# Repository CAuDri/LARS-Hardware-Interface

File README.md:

# LARS Hardware Interface

This repository contains the schematic, PCB design files and a basic firmware stack for the Hardware Interface of the [Lightweight Autonomous Racing System (LARS)](https://github.com/CAuDri/LARS). 

The board is based on a STM32F4 microcontroller and is designed to interface with various sensors and actuators on the vehicle. The communication with the host PC is done via USB, using [micro-ROS](https://micro.ros.org/) and the underlying [micro-XRCE DDS](https://micro-xrce-dds.docs.eprosima.com/en/latest/).

## License

This project is licensed under the [GNU General Public License v3.0](https://www.gnu.org/licenses/gpl-3.0.en.html). You can freely use, modify, and distribute this code as long as you comply with the terms of the license.

The hardware design files are released under the [CERN Open Hardware Licence v2](https://ohwr.org/cernohl/).

# Hardware

##  Features

### General
- STM32F429 microcontroller (Cortex-M4, 180MHz, 2MB Flash, 256KB RAM)
- Board dimensions: 86 x 86 mm
- SWD interface for programming and debugging
- Boot-/Reset header for flashing via USB
- User- and Reset buttons
- RGB Debug LEDs

### Power
- 5V power supply via XT30 connector or USB (XT30 will be prioritized)
- Power input range: **4.8V - 5.3V**
- "Reverse polarity protection"
- On-board 3.3V voltage regulator
- Switchable 5V output for external devices
- Additional 3.3V and 5V output

### Interfaces
- 2x USB-C (2.0 Fullspeed) for host PC and debugging/flashing
- CAN-Bus (with optional termination)
- 8x I2C
- 3x UART
- 2x SPI
- 2x Servo (with analog feedback)
- 2x WS2812 LED strip 
- Buffered and filtered analog inputs
- Additional Timer channels and GPIOs
- 3.3V and 5V output for external devices

### Protection
- 4A/8A polyfuse on the main power input
- "Rudimentary" reverse polarity protection
- Back-power protection for both power inputs (USB and XT30)
- TVS diodes against voltage spikes on all power rails
- Current limited 5V output (max 2.4 A)
- All data lines are 5V tolerant
- Additional short-circuit, overcurrent and -voltage protection up to ~20V on all interfaces

## PCB-Files

The board was designed in KiCad 9.0. The project file can be found in the `/PCB/KiCad` directory.

Link to the [Schematic](https://github.com/CAuDri/LARS-Hardware-Interface/blob/main/PCB/schematic.pdf).

All PCB design files, a bill of materials and Gerber Files for manufacturing at [JLCPCB](https://jlcpcb.com/) can be found in the `/PCB/manufacturing` directory. They have been exported using the [Fabrication Toolkit](https://github.com/bennymeg/Fabrication-Toolkit) KiCad plugin.

A 3D STEP model of the board can be found in the `/PCB/export` directory.

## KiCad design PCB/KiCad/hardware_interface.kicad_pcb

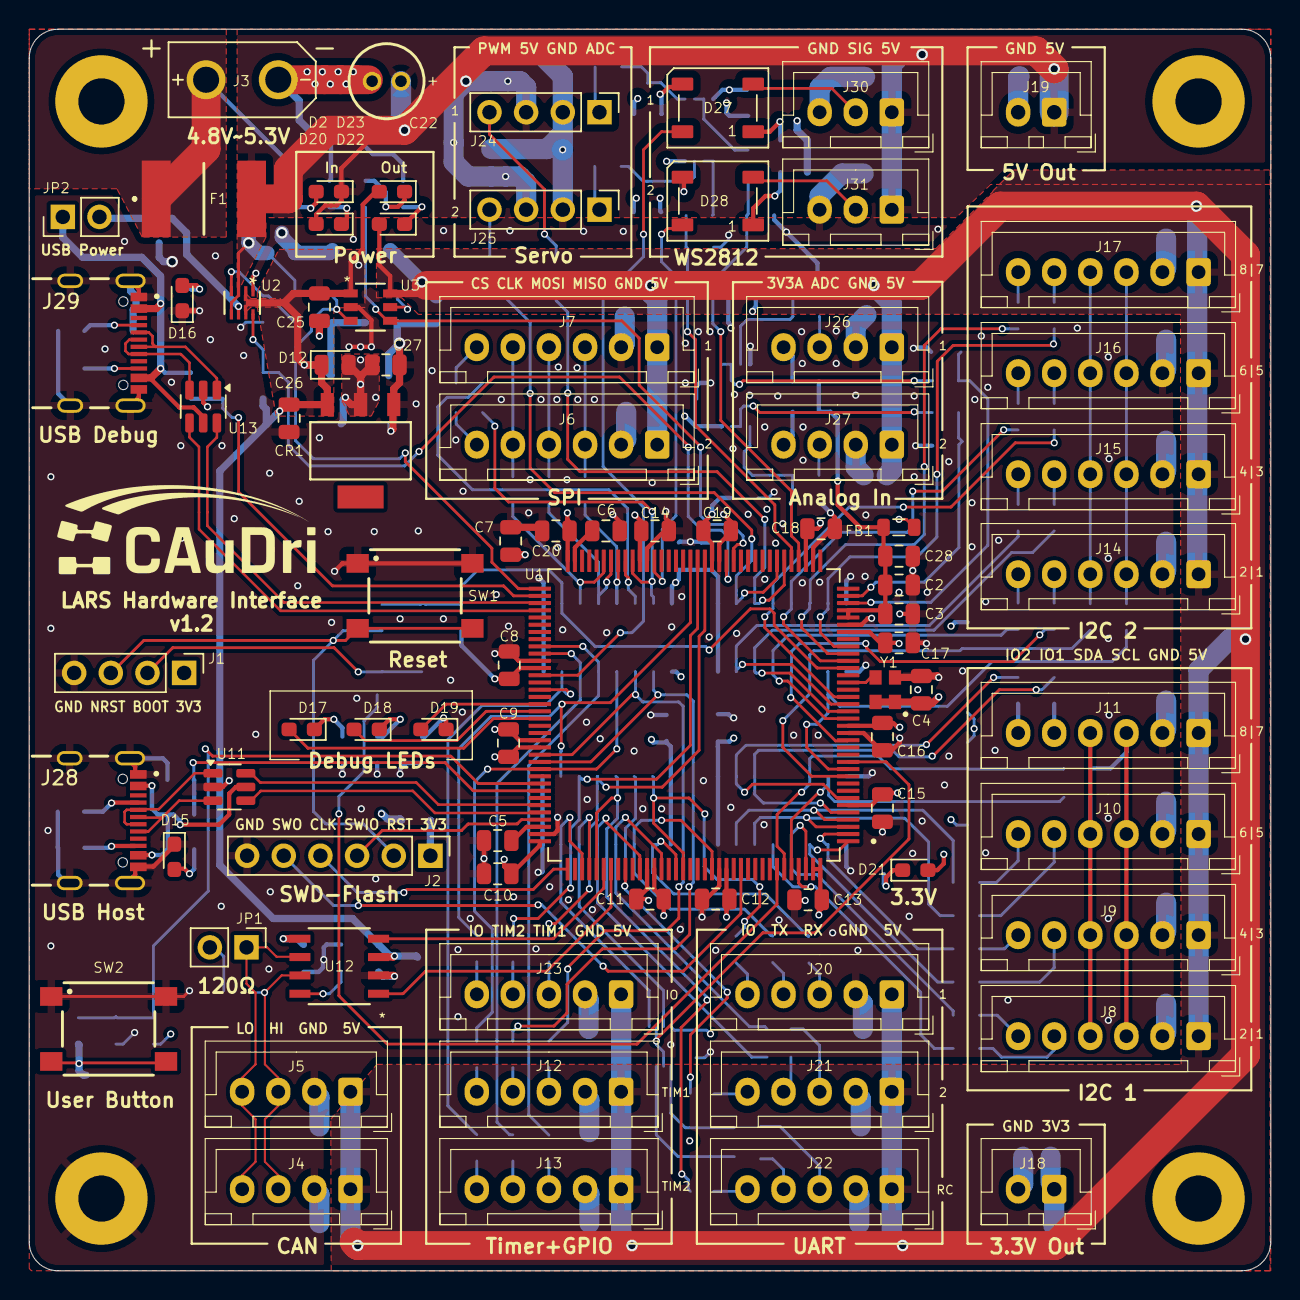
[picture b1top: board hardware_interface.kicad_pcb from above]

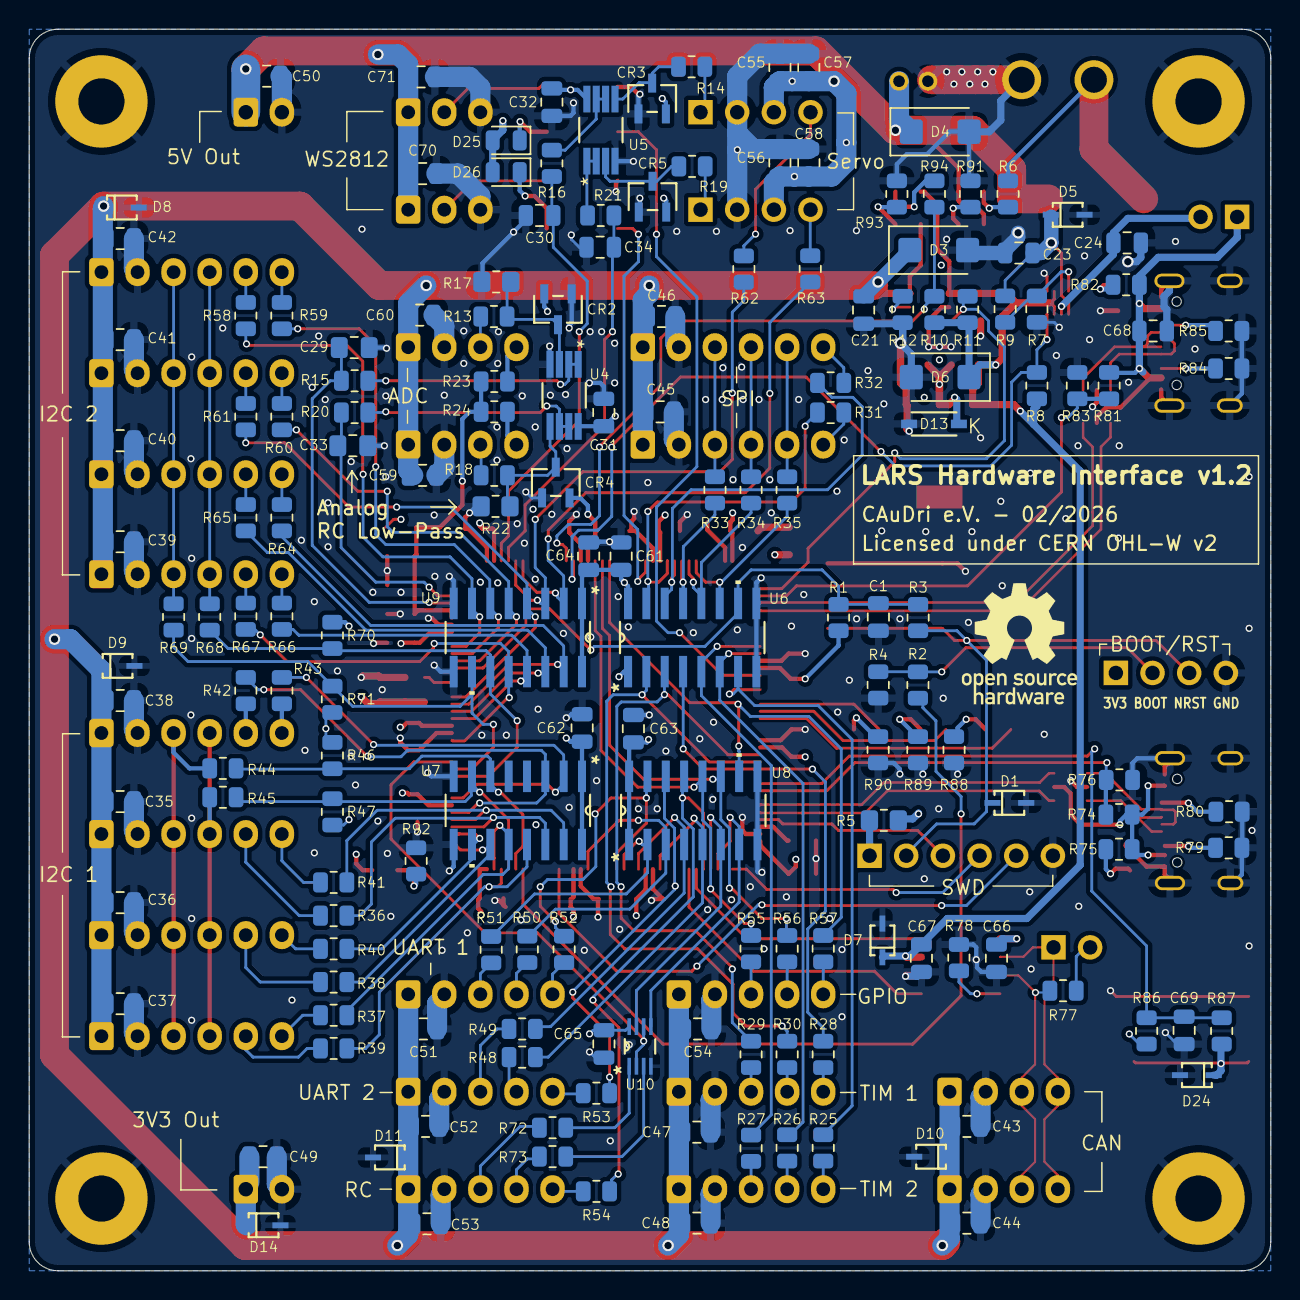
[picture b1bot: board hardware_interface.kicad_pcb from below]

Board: 6 copper layers, 86.0 x 86.0 mm, 255 parts (168 on the bottom side), 178 nets.

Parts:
C1, C3, C4, C8, C9, C10, C11, C12, C13, C14, C15, C16, C17, C18, C19, C20, C30, C31, C32, C34, C35, C36, C37, C38, C39, C40, C41, C42, C43, C44, C45, C46, C47, C48, C49, C50, C51, C52, C53, C54, C57, C58, C59, C60, C61, C62, C63, C64, C65, C66, C67, C70, C71: 100n; C_0805_2012Metric
C2, C5, C6, C24, C26, C68, C69: 2u2; C_0805_2012Metric
C7, C21, C23, C25, C27, C55, C56: 10u; C_0805_2012Metric
C22: 100u; 860020372006
C28: 10n; C_0805_2012Metric
C29, C33: NA; C_0805_2012Metric_Pad1.18x1.45mm_HandSolder
CR1: LD1117AS33TR
CR2, CR3, CR4, CR5: BAT54SFILM
D1, D5, D7, D8, D9, D10, D11, D14, D24: TVS; STS321050U182
D2, D17, D23: Red; LED_0603_1608Metric_Red
D3, D4, D6: 5V6; Z1SMA5.6
D12, D25, D26: 0.7V; D_0805_2012Metric
D13: 3V3; BZT52C3V3
D15, D16, D18, D20, D21, D22: Green; LED_0603_1608Metric_Green
D19: Blue; LED_0603_1608Metric_Blue
D27, D28: WS2812B; LED_WS2812B_PLCC4_5.0x5.0mm_P3.2mm
F1: 2920L400; 2920L400_15MR
FB1: FBMH2012HM221-T8; L_0805_2012Metric
G1: CAuDri-Logo; CAuDri Logo
G2: LOGO; OSHWA Logo
H1, H2, H3, H4: MountingHole; MountingHole_3.2mm_M3_Pad
J1: Reset Header; PinHeader_1x04_P2.54mm_Vertical
J2: SWD Flash; PinHeader_1x06_P2.54mm_Vertical
J3: XT30; XT30UPB-M
J4, J5: CAN1; JST_XH_B4B-XH-A_1x04_P2.50mm_Vertical
J6, J7: SPI1; JST_XH_B6B-XH-A_1x06_P2.50mm_Vertical
J8, J9, J10, J11: I2C1; JST_XH_B6B-XH-A_1x06_P2.50mm_Vertical
J12: TIM1; JST_XH_B5B-XH-A_1x05_P2.50mm_Vertical
J13: TIM2; JST_XH_B5B-XH-A_1x05_P2.50mm_Vertical
J14, J15, J16, J17: I2C2; JST_XH_B6B-XH-A_1x06_P2.50mm_Vertical
J18: 3.3V Out; JST_XH_B2B-XH-A_1x02_P2.50mm_Vertical
J19: 5V Out; JST_XH_B2B-XH-A_1x02_P2.50mm_Vertical
J20: UART1; JST_XH_B5B-XH-A_1x05_P2.50mm_Vertical
J21: UART2; JST_XH_B5B-XH-A_1x05_P2.50mm_Vertical
J22: RC; JST_XH_B5B-XH-A_1x05_P2.50mm_Vertical
J23: GPIO; JST_XH_B5B-XH-A_1x05_P2.50mm_Vertical
J24: Servo 1; PinHeader_1x04_P2.54mm_Vertical
J25: Servo 2; PinHeader_1x04_P2.54mm_Vertical
J26: Analog 1; JST_XH_B4B-XH-A_1x04_P2.50mm_Vertical
J27: Analog 2; JST_XH_B4B-XH-A_1x04_P2.50mm_Vertical
J28: USB1; GCT_USB4105-GF-A
J29: USB2; GCT_USB4105-GF-A
J30: LED1; JST_XH_B3B-XH-A_1x03_P2.50mm_Vertical
J31: LED2; JST_XH_B3B-XH-A_1x03_P2.50mm_Vertical
JP1: CAN1; PinHeader_1x02_P2.54mm_Jumper
JP2: USB Power; PinHeader_1x02_P2.54mm_Jumper
R1, R4, R7, R86: 10k; R_0805_2012Metric
R2, R6, R9, R13, R14, R16, R18, R19, R21, R74, R78, R81, R87, R88, R89, R90, R91, R92, R93, R94: 1k; R_0805_2012Metric
R3, R15, R20, R25, R26, R27, R28, R29, R30, R31, R32, R33, R34, R35, R36, R37, R38, R39, R40, R41, R42, R43, R48, R49, R50, R51, R52, R53, R54, R55, R56, R57, R58, R59, R60, R61, R62, R63, R64, R65, R66, R67, R72, R73, R75, R82: 220; R_0805_2012Metric
R5: 0R; R_0805_2012Metric_Pad1.20x1.40mm_HandSolder
R8, R10, R11, R79, R80, R84, R85: 5k1; R_0805_2012Metric
R12, R23, R24, R44, R45, R68, R69, R77: 120; R_0805_2012Metric
R17, R22: NA; R_0805_2012Metric_Pad1.20x1.40mm_HandSolder
R46, R47, R70, R71, R76, R83: 2k2; R_0805_2012Metric
SW1: Reset; 430182043816
SW2: User Button; 430182043816
U1: STM32F429ZIT6TR
U2: TPS2117DRLR; PTPS2117DRLR
U3: MIC2039AYM6-TR
U4, U5: OPA2834IDGKR
U6, U7, U8, U9: SN74S1051DR
U10: SN74LVC2G86DCUR; SN74LVC2G86
U11, U13: USBLC6-2SC6; SOT-23-6
U12: TCAN1057AVDRQ1
Y1: IQXO-791 8.00MHz; WE-SPXO_IQXO-791

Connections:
5V_USB: C24.1, JP2.2 (B), U2.6 (VIN2)
+3V3: C4.1, C7.1, C8.1, C9.1, C10.1, C11.1, C12.1, C13.1, C14.1, C15.1, C16.1, C17.1, C18.1, C19.1, C20.1, C27.1, C31.1, C32.1, C49.1, C61.1, C62.1, C63.1, C64.1, C65.1, C66.1, CR1.2 (VOUT), CR2.2, CR3.2, CR4.2, CR5.2, D12.2 (A), D13.1 (K), D14.1 (K), D21.2 (A), FB1.1, J1.1, J18.1, R1.2, R5.2, R46.2, R47.2, R70.2, R71.2, R86.1, U1.6 (VBAT), U1.17 (VDD), U1.30 (VDD), U1.39 (VDD), U1.52 (VDD), U1.62 (VDD), U1.72 (VDD), U1.84 (VDD), U1.95 (VDD), U1.108 (VDD), U1.121 (VDD), U1.131 (VDD), U1.143 (PDR_ON), U1.144 (VDD), U4.8 (VS+), U5.8 (VS+), U6.1 (VCC), U6.16 (VCC), U7.1 (VCC), U7.16 (VCC), U8.1 (VCC), U8.16 (VCC), U9.1 (VCC), U9.16 (VCC), U10.8 (VCC), U12.5 (VIO), Y1.1 (E/D), Y1.4 (+VS)
+3V3A: C2.1, C3.1, C28.1, FB1.2, R23.2, R24.2, U1.32 (VREF+), U1.33 (VDDA)
+5V: C25.1, C26.1, C67.1, CR1.3 (VIN), D6.1 (K), D7.1 (K), D12.1 (K), D23.2 (A), D25.2 (A), D26.2 (A), R8.1, R10.2, R11.2, U2.2 (VOUT), U2.7 (VOUT), U3.1 (VIN), U12.3 (VCC)
+5V_OUT: C21.1, C35.1, C36.1, C37.1, C38.1, C39.1, C40.1, C41.1, C42.1, C43.1, C44.1, C45.1, C46.1, C47.1, C48.1, C51.1, C52.1, C53.1, C54.1, C59.1, C60.1, D3.1 (K), D8.1 (K), D9.1 (K), D10.1 (K), D11.1 (K), D22.2 (A), J4.1, J5.1, J6.1, J7.1, J8.1, J9.1, J10.1, J11.1, J12.1, J13.1, J14.1, J15.1, J16.1, J17.1, J20.1, J21.1, J22.1, J23.1, J26.1, J27.1, U3.6 (VOUT)
+5V_PS: C22.1, C23.1, C50.1, C55.1, C56.1, C57.1, C58.1, C70.1, C71.1, D2.1 (K), D4.1 (K), D5.1 (K), D20.2 (A), F1.2, J19.1, J24.3, J25.3, J30.1, J31.1, R9.2, U2.3 (VIN1), U2.5 (MODE)
/Analog/ANALOG1_OP_IN: CR2.3, R13.2, R17.1, U4.3 (VIN1+)
/Analog/ANALOG1_OP_OUT: R15.1, U4.1 (VOUT1), U4.2 (VIN1-)
/Analog/ANALOG2_OP_IN: CR4.3, R18.2, R22.1, U4.5 (VIN2+)
/Analog/ANALOG2_OP_OUT: R20.1, U4.6 (VIN2-), U4.7 (VOUT2)
/Analog/SERVO1_OP_IN: CR3.3, R14.2, U5.5 (VIN2+)
/Analog/SERVO1_OP_OUT: R16.1, U5.6 (VIN2-), U5.7 (VOUT2)
/Analog/SERVO2_OP_IN: CR5.3, R19.2, U5.3 (VIN1+)
/Analog/SERVO2_OP_OUT: R21.1, U5.1 (VOUT1), U5.2 (VIN1-)
/LEDs/LED1_OUT: D27.2 (DOUT), J30.2
/LEDs/LED1_VDD: D25.1 (K), D27.1 (VDD)
/LEDs/LED2_OUT: D28.2 (DOUT), J31.2
/LEDs/LED2_VDD: D26.1 (K), D28.1 (VDD)
/LEDs/LED_3V3: D21.1 (K), R92.1
/LEDs/LED_5V_OUT: D22.1 (K), R93.1
/LEDs/LED_5V_PS: D20.1 (K), R91.1
/LEDs/LED_BLUE: D19.1 (K), R90.1
/LEDs/LED_EXT_OC: D23.1 (K), R94.1
/LEDs/LED_GREEN: D18.1 (K), R89.1
/LEDs/LED_RED: D17.1 (K), R88.1
/LEDs/USER_BTN: D24.1 (K), R87.2, SW2.2
/Microcontroller/BOOT0: J1.2, R2.1, R4.2
/Microcontroller/RESET: D1.1 (K), J1.3, J2.2, R3.1, SW1.2
/Microcontroller/STM_BOOT0: R2.2, U1.138 (BOOT0)
/Microcontroller/STM_OSC_IN: U1.23 (PH0), Y1.3 (OUT)
/Microcontroller/STM_VCAP1: C6.1, U1.71 (VCAP_1)
/Microcontroller/STM_VCAP2: C5.1, U1.106 (VCAP_2)
/Power Distribution/MUX_PR1: R7.1, R9.1, U2.4 (PR1)
/Power Distribution/PS_ILIMIT: R12.1, U3.5 (ILIMIT)
/Power Distribution/PWR_IN: F1.1, J3.2 (PWR), R6.2
/USB + CAN Bus/USB1_CC1: J28.A5 (CC1), R80.1
/USB + CAN Bus/USB1_CC2: J28.B5 (CC2), R79.1
/USB + CAN Bus/USB1_D_IN+: J28.A6 (D+), J28.B6 (D+), U11.3 (I/O2)
/USB + CAN Bus/USB1_D_IN-: J28.A7 (D-), J28.B7 (D-), U11.1 (I/O1)
/USB + CAN Bus/USB1_VBUS_IN: J28.A4_B9 (VBUS), J28.B4_A9 (VBUS), R74.2, R75.1, U11.5 (VBUS)
/USB + CAN Bus/USB2_CC1: J29.A5 (CC1), R85.1
/USB + CAN Bus/USB2_CC2: J29.B5 (CC2), R84.1
/USB + CAN Bus/USB2_D_IN+: J29.A6 (D+), J29.B6 (D+), U13.3 (I/O2)
/USB + CAN Bus/USB2_D_IN-: J29.A7 (D-), J29.B7 (D-), U13.1 (I/O1)
/USB + CAN Bus/USB2_VBUS_IN: C68.1, J29.A4_B9 (VBUS), J29.B4_A9 (VBUS), JP2.1 (A), R81.2, R82.1, U13.5 (VBUS)
ANALOG_IN1: J26.3, R13.1
ANALOG_IN1': C29.1, R15.2, U1.34 (PA0)
ANALOG_IN2: J27.3, R18.1
ANALOG_IN2': C33.1, R20.2, U1.35 (PA1)
CAN1_N: J4.4, J5.4, JP1.1 (A), U12.6 (CANL)
CAN1_P: J4.3, J5.3, R77.1, U12.7 (CANH)
CAN1_RX: U1.114 (PD0), U12.4 (RXD)
CAN1_TX: U1.115 (PD1), U12.1 (TXD)
DEBUG_LED_BLUE: D19.2 (A), U1.89 (PG4)
DEBUG_LED_GREEN: D18.2 (A), U1.90 (PG5)
DEBUG_LED_RED: D17.2 (A), U1.91 (PG6)
GND: C1.2, C2.2, C3.2, C4.2, C5.2, C6.2, C7.2, C8.2, C9.2, C10.2, C11.2, C12.2, C13.2, C14.2, C15.2, C16.2, C17.2, C18.2, C19.2, C20.2, C21.2, C22.2, C23.2, C24.2, C25.2, C26.2, C27.2, C28.2, C29.2, C30.2, C31.2, C32.2, C33.2, C34.2, C35.2, C36.2, C37.2, C38.2, C39.2, C40.2, C41.2, C42.2, C43.2, C44.2, C45.2, C46.2, C47.2, C48.2, C49.2, C50.2, C51.2, C52.2, C53.2, C54.2, C55.2, C56.2, C57.2, C58.2, C59.2, C60.2, C61.2, C62.2, C63.2, C64.2, C65.2, C66.2, C67.2, C68.2, C69.2, C70.2, C71.2, CR1.1 (GND), CR2.1, CR3.1, CR4.1, CR5.1, D1.2 (A), D3.2 (A), D4.2 (A), D5.2 (A), D6.2 (A), D7.2 (A), D8.2 (A), D9.2 (A), D10.2 (A), D11.2 (A), D13.2 (A), D14.2 (A), D15.1 (K), D16.1 (K), D24.2 (A), D27.3 (VSS), D28.3 (VSS), H1.1, H2.1, H3.1, H4.1, J1.4, J2.6, J3.1 (GND), J4.2, J5.2, J6.2, J7.2, J8.2, J9.2, J10.2, J11.2, J12.2, J13.2, J14.2, J15.2, J16.2, J17.2, J18.2, J19.2, J20.2, J21.2, J22.2, J23.2, J24.2, J25.2, J26.2, J27.2, J28.A1_B12 (GND), J28.B1_A12 (GND), J28.S1 (SHIELD), J29.A1_B12 (GND), J29.B1_A12 (GND), J29.S1 (SHIELD), J30.3, J31.3, R4.1, R7.2, R12.2, R17.2, R22.2, R76.2, R78.1, R79.2, R80.2, R83.2, R84.2, R85.2, R88.2, R89.2, R90.2, R91.2, R92.2, R93.2, SW1.1, SW2.1, U1.16 (VSS), U1.31 (VSSA), U1.38 (VSS), U1.51 (VSS), U1.61 (VSS), U1.83 (VSS), U1.94 (VSS), U1.107 (VSS), U1.120 (VSS), U1.130 (VSS), U2.1 (GND), U3.2 (GND), U4.4 (VS-), U5.4 (VS-), U6.8 (GND), U6.9 (GND), U7.8 (GND), U7.9 (GND), U8.8 (GND), U8.9 (GND), U9.8 (GND), U9.9 (GND), U10.4 (GND), U11.2 (GND), U12.2 (GND), U13.2 (GND), Y1.2 (GND)
GPIO1: J23.3, R55.2
GPIO1': R55.1, U1.53 (PF13), U8.12 (D09)
GPIO2: J23.4, R56.2
GPIO2': R56.1, U1.54 (PF14), U8.11 (D08)
GPIO3: J23.5, R57.2
GPIO3': R57.1, U1.55 (PF15), U8.10 (D07)
I2C1_IO1: J8.5, R39.2
I2C1_IO1': R39.1, U1.141 (PE0), U7.13 (D10)
I2C1_IO2: J8.6, R38.2
I2C1_IO2': R38.1, U1.142 (PE1), U7.12 (D09)
I2C1_IO3: J9.5, R37.2
I2C1_IO3': R37.1, U1.1 (PE2), U7.11 (D08)
I2C1_IO4: J9.6, R36.2
I2C1_IO4': R36.1, U1.2 (PE3), U7.10 (D07)
I2C1_IO5: J10.5, R40.2
I2C1_IO5': R40.1, U1.3 (PE4), U7.14 (D11)
I2C1_IO6: J10.6, R41.2
I2C1_IO6': R41.1, U1.4 (PE5), U7.15 (D12)
I2C1_IO7: J11.5, R43.2
I2C1_IO7': R43.1, U1.5 (PE6), U7.3 (D02)
I2C1_IO8: J11.6, R42.2
I2C1_IO8': R42.1, U1.7 (PC13), U7.2 (D01)
I2C1_SCL: J8.3, J9.3, J10.3, J11.3, R44.2
I2C1_SCL': R44.1, R46.1, U1.139 (PB8), U7.6 (D05)
I2C1_SDA: J8.4, J9.4, J10.4, J11.4, R45.2
I2C1_SDA': R45.1, R47.1, U1.140 (PB9), U7.7 (D06)
I2C2_IO1: J14.5, R67.2
I2C2_IO1': R67.1, U1.15 (PF5), U9.12 (D09)
I2C2_IO2: J14.6, R66.2
I2C2_IO2': R66.1, U1.18 (PF6), U9.13 (D10)
I2C2_IO3: J15.5, R65.2
I2C2_IO3': R65.1, U1.19 (PF7), U9.14 (D11)
I2C2_IO4: J15.6, R64.2
I2C2_IO4': R64.1, U1.20 (PF8), U9.15 (D12)
I2C2_IO5: J16.5, R61.2
I2C2_IO5': R61.1, U1.21 (PF9), U9.4 (D03)
I2C2_IO6: J16.6, R60.2
I2C2_IO6': R60.1, U1.26 (PC0), U9.5 (D04)
I2C2_IO7: J17.5, R58.2
I2C2_IO7': R59.1, U1.27 (PC1), U9.6 (D05)
I2C2_IO8: J17.6, R59.2
I2C2_IO8': R58.1, U1.28 (PC2), U9.7 (D06)
I2C2_SCL: J14.3, J15.3, J16.3, J17.3, R69.2
I2C2_SCL': R69.1, R71.1, U1.11 (PF1), U9.10 (D07)
I2C2_SDA: J14.4, J15.4, J16.4, J17.4, R68.2
I2C2_SDA': R68.1, R70.1, U1.10 (PF0), U9.11 (D08)
LED1_PWM: D27.4 (DIN), U1.85 (PD14)
LED2_PWM: D28.4 (DIN), U1.60 (PE9)
unnamed: D2.2 (A), R6.1
unnamed: D15.2 (A), R75.2
unnamed: D16.2 (A), R82.2
unnamed: J2.1, R5.1
unnamed: J26.4, R23.1
unnamed: J27.4, R24.1
unnamed: JP1.2 (B), R77.2
unnamed: R72.1, U10.1 (1A)
unnamed: R73.1, U10.3 (2Y)
unnamed: R78.2, U12.8 (S)
PWR_EXT_EN: R11.1, U1.73 (PB12), U3.3 (EN)
PWR_EXT_FAULT: R10.1, R94.2, U1.49 (PF11), U3.4 (*FAULT)
PWR_STATUS: R8.2, U1.50 (PF12), U2.8 (ST)
RC_INVERT: U1.12 (PF2), U10.2 (1B), U10.6 (2B)
RC_IO: J22.5, R54.2
RC_IO': R54.1, U1.113 (PC12), U8.13 (D10)
RC_RX: J22.3, R72.2
RC_RX': U1.112 (PC11), U8.6 (D05), U10.7 (1Y)
RC_TX: J22.4, R73.2
RC_TX': U1.111 (PC10), U8.7 (D06), U10.5 (2A)
SERVO1_ADC: J24.1, R14.1
SERVO1_ADC': C30.1, R16.2, U1.40 (PA4)
SERVO1_PWM: J24.4, R62.2
SERVO1_PWM': R62.1, U1.42 (PA6), U9.3 (D02)
SERVO2_ADC: J25.1, R19.1
SERVO2_ADC': C34.1, R21.2, U1.41 (PA5)
SERVO2_PWM: J25.4, R63.2
SERVO2_PWM': R63.1, U1.43 (PA7), U9.2 (D01)
SPI1_CS1: J6.6, R31.2
SPI1_CS1': R31.1, U1.63 (PE10), U6.15 (D12)
SPI1_CS2: J7.6, R32.2
SPI1_CS2': R32.1, U1.64 (PE11), U6.14 (D11)
SPI1_MISO: J6.4, J7.4, R34.2
SPI1_MISO': R34.1, U1.66 (PE13), U6.12 (D09)
SPI1_MOSI: J6.5, J7.5, R35.2
SPI1_MOSI': R35.1, U1.67 (PE14), U6.11 (D08)
SPI1_SCLK: J6.3, J7.3, R33.2
SPI1_SCLK': R33.1, U1.65 (PE12), U6.13 (D10)
STM_NRST: C1.1, R1.1, R3.2, U1.25 (~NRST), U6.10 (D07)
SWD_SWCLK: J2.4, U1.109 (PA14)
SWD_SWIO: J2.3, U1.105 (PA13)
SWD_SWO: J2.5, U1.133 (PB3)
TIM1_CH1: J12.3, R29.2
TIM1_CH1': R29.1, U1.96 (PC6), U6.3 (D02)
TIM1_CH2: J12.4, R30.2
TIM1_CH2': R30.1, U1.97 (PC7), U6.2 (D01)
TIM1_IO: J12.5, R28.2
TIM1_IO': R28.1, U1.98 (PC8), U6.4 (D03)
TIM2_CH1: J13.3, R27.2
TIM2_CH1': R27.1, U1.81 (PD12), U6.5 (D04)
TIM2_CH2: J13.4, R26.2
TIM2_CH2': R26.1, U1.82 (PD13), U6.6 (D05)
TIM2_IO: J13.5, R25.2
TIM2_IO': R25.1, U1.87 (PG2), U6.7 (D06)
UART1_IO: J20.5, R52.2
UART1_IO': R52.1, U1.125 (PG10), U8.15 (D12)
UART1_RX: J20.3, R51.2
UART1_RX': R51.1, U1.124 (PG9), U8.2 (D01)
UART1_TX: J20.4, R50.2
UART1_TX': R50.1, U1.129 (PG14), U8.3 (D02)
UART2_IO: J21.5, R53.2
UART2_IO': R53.1, U1.117 (PD3), U8.14 (D11)
UART2_RX: J21.3, R49.2
UART2_RX': R49.1, U1.122 (PD6), U8.4 (D03)
UART2_TX: J21.4, R48.2
UART2_TX': R48.1, U1.119 (PD5), U8.5 (D04)
USB1_D+: U1.104 (PA12), U11.4 (I/O2)
USB1_D-: U1.103 (PA11), U11.6 (I/O1)
USB1_VBUS: R74.1, R76.1, U1.101 (PA9)
USB2_D+: U1.76 (PB15), U13.4 (I/O2)
USB2_D-: U1.75 (PB14), U13.6 (I/O1)
USB2_VBUS: R81.1, R83.1, U1.74 (PB13)
USER_BUTTON: C69.1, R86.2, R87.1, U1.100 (PA8)

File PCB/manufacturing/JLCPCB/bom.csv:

Designator,Footprint,Quantity,Value,LCSC Part #
"C1, C10, C11, C12, C13, C14, C15, C16, C17, C18, C19, C20, C3, C30, C31, C32, C34, C35, C36, C37, C38, C39, C4, C40, C41, C42, C43, C44, C45, C46, C47, C48, C49, C50, C51, C52, C53, C56, C57, C58, C59, C60, C61, C62, C63, C64, C65, C66, C69, C70, C8, C9",0805,52,100n,
"C2, C24, C26, C5, C6, C67, C68",0805,7,2u2,
"C21, C23, C25, C27, C54, C55, C7",0805,7,10u,
C22,860020372006,1,100u,
C28,0805,1,10n,
CR1,LD1117AS33TR,1,LD1117AS33TR,
"CR2, CR3, CR4, CR5",BAT54SFILM,4,BAT54SFILM,
"D1, D15, D9",0603,3,Red,
"D10, D12, D13, D14, D7, D8",0603,6,Green,
D11,0603,1,Blue,
"D16, D17, D5",0805,3,0.7V,
"D18, D19",LED_WS2812B_PLCC4_5.0x5.0mm_P3.2mm,2,WS2812B,
"D2, D3, D4",Z1SMA5.6,3,5V6,
D6,BZT52C3V3,1,3V3,
F1,2920L400_15MR,1,2920L400,
FB1,0805,1,FBMH2012HM221-T8,
G1,CAuDri Logo,1,CAuDri-Logo,
J1,PinHeader_1x04_P2.54mm_Vertical,1,Reset Header,
"J10, J11, J8, J9",JST_XH_B6B-XH-A_1x06_P2.50mm_Vertical,4,I2C1,
J12,JST_XH_B5B-XH-A_1x05_P2.50mm_Vertical,1,TIM1,
J13,JST_XH_B5B-XH-A_1x05_P2.50mm_Vertical,1,TIM2,
"J14, J15, J16, J17",JST_XH_B6B-XH-A_1x06_P2.50mm_Vertical,4,I2C2,
J18,JST_XH_B2B-XH-A_1x02_P2.50mm_Vertical,1,3.3V Out,
J19,JST_XH_B2B-XH-A_1x02_P2.50mm_Vertical,1,5V Out,
J2,PinHeader_1x06_P2.54mm_Vertical,1,SWD Flash,
J20,JST_XH_B5B-XH-A_1x05_P2.50mm_Vertical,1,UART1,
J21,JST_XH_B5B-XH-A_1x05_P2.50mm_Vertical,1,UART2,
J22,JST_XH_B5B-XH-A_1x05_P2.50mm_Vertical,1,UART3,
J23,PinHeader_1x04_P2.54mm_Vertical,1,Servo 1,
J24,PinHeader_1x04_P2.54mm_Vertical,1,Servo 2,
J25,JST_XH_B5B-XH-A_1x05_P2.50mm_Vertical,1,GPIO,
J26,JST_XH_B4B-XH-A_1x04_P2.50mm_Vertical,1,Analog 1,
J27,JST_XH_B4B-XH-A_1x04_P2.50mm_Vertical,1,Analog 2,
J28,GCT_USB4105-GF-A,1,USB1,
J29,GCT_USB4105-GF-A,1,USB2,
J3,XT30UPB-M,1,XT30,
J30,JST_XH_B3B-XH-A_1x03_P2.50mm_Vertical,1,LED1,
J31,JST_XH_B3B-XH-A_1x03_P2.50mm_Vertical,1,LED2,
"J4, J5",JST_XH_B4B-XH-A_1x04_P2.50mm_Vertical,2,CAN1,
"J6, J7",JST_XH_B6B-XH-A_1x06_P2.50mm_Vertical,2,SPI1,
JP1,PinHeader_1x02_P2.54mm_Jumper,1,CAN1,
JP2,PinHeader_1x02_P2.54mm_Jumper,1,USB Power,
"R1, R4, R7, R86",0805,4,10k,
"R10, R11, R8",0805,3,4k7,
"R12, R23, R24, R45, R46, R70, R71, R77",0805,8,120,
"R13, R14, R16, R18, R19, R2, R21, R76, R78, R83, R9",0805,11,1k,
"R15, R20, R25, R26, R27, R28, R29, R30, R31, R32, R33, R34, R35, R36, R37, R38, R39, R40, R41, R42, R43, R44, R49, R50, R51, R52, R53, R54, R55, R56, R57, R58, R59, R60, R61, R62, R63, R64, R65, R66, R67, R68, R69, R75, R82, R88, R89, R90, R92",0805,49,220,
"R3, R6, R74, R81, R87, R91, R93, R94",0805,8,470,
"R47, R48, R72, R73",0805,4,2k2,
R5,0805,1,0R,
"R79, R80, R84, R85",0805,4,5k1,
SW1,430182043816,1,Reset,
SW2,430182043816,1,User Button,
U1,STM32F429ZIT6TR,1,STM32F429ZIT6TR,
"U10, U12",SOT-23-6,2,USBLC6-2SC6,
U11,TCAN1057AVDRQ1,1,TCAN1057AVDRQ1,
U2,PTPS2117DRLR,1,TPS2117DRLR,
U3,MIC2039AYM6-TR,1,MIC2039AYM6-TR,
"U4, U5",OPA2834IDGKR,2,OPA2834IDGKR,
"U6, U7, U8, U9",SN74S1051DR,4,SN74S1051DR,
Y1,WE-SPXO_IQXO-791,1,IQXO-791 8.00MHz,

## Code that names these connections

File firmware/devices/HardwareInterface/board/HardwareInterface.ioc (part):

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Mcu.Name=STM32F429ZITx
Mcu.Package=LQFP144
Mcu.UserName=STM32F429ZITx
PA0/WKUP.GPIOParameters=GPIO_Label
PA0/WKUP.GPIO_Label=ANALOG_IN1
PA0/WKUP.Signal=ADCx_IN0
PA1.GPIOParameters=GPIO_Label
PA1.GPIO_Label=ANALOG_IN2
PA1.Signal=ADCx_IN1
PA11.GPIOParameters=GPIO_Label
PA11.GPIO_Label=USB1_D-
PA11.Mode=Device_Only
PA11.Signal=USB_OTG_FS_DM
PA12.GPIOParameters=GPIO_Label
PA12.GPIO_Label=USB1_D+
PA12.Mode=Device_Only
PA12.Signal=USB_OTG_FS_DP
PA13.GPIOParameters=GPIO_Label
PA13.GPIO_Label=SWD_SWDIO
PA13.Mode=Trace_Asynchronous_SW
PA13.Signal=SYS_JTMS-SWDIO
PA14.GPIOParameters=GPIO_Label
PA14.GPIO_Label=SWD_SWCLK
PA14.Mode=Trace_Asynchronous_SW
PA14.Signal=SYS_JTCK-SWCLK
PA4.GPIOParameters=GPIO_Label
PA4.GPIO_Label=SERVO1_ADC
PA4.Signal=ADCx_IN4
PA5.GPIOParameters=GPIO_Label
PA5.GPIO_Label=SERVO2_ADC
PA5.Signal=ADCx_IN5
PA6.GPIOParameters=GPIO_Label
PA6.GPIO_Label=SERVO1_PWM
PA6.Signal=S_TIM3_CH1
PA7.GPIOParameters=GPIO_Label
PA7.GPIO_Label=SERVO2_PWM
PA7.Signal=S_TIM3_CH2
PA8.GPIOParameters=GPIO_Label,GPIO_ModeDefaultEXTI
PA8.GPIO_Label=USER_BUTTON
PA8.GPIO_ModeDefaultEXTI=GPIO_MODE_IT_RISING_FALLING
PA8.Signal=GPXTI8
PA9.GPIOParameters=GPIO_Label
PA9.GPIO_Label=USB1_VBUS
PA9.Mode=Activate_VBUS
PA9.Signal=USB_OTG_FS_VBUS
PB12.GPIOParameters=GPIO_Label
PB12.GPIO_Label=PWR_EXT_ENABLE
PB12.Signal=GPIO_Output
PB13.GPIOParameters=GPIO_Label
PB13.GPIO_Label=USB2_VBUS
PB13.Mode=Activate_VBUS_FS
PB13.Signal=USB_OTG_HS_VBUS
PB14.GPIOParameters=GPIO_Label
PB14.GPIO_Label=USB2_D-
PB14.Mode=Device_Only_FS
PB14.Signal=USB_OTG_HS_DM
PB15.GPIOParameters=GPIO_Label
PB15.GPIO_Label=USB2_D+
PB15.Mode=Device_Only_FS
PB15.Signal=USB_OTG_HS_DP
PB3.GPIOParameters=GPIO_Label
PB3.GPIO_Label=SWD_SWO
PB3.Mode=Trace_Asynchronous_SW
PB3.Signal=SYS_JTDO-SWO
PB8.Mode=I2C
PB8.Signal=I2C1_SCL
PB9.Mode=I2C
PB9.Signal=I2C1_SDA
PC0.GPIOParameters=GPIO_Label
PC0.GPIO_Label=I2C2_GPIO6
PC0.Signal=GPIO_Analog
PC1.GPIOParameters=GPIO_Label
PC1.GPIO_Label=I2C2_GPIO7
PC1.Signal=GPXTI1
PC10.Mode=Asynchronous
PC10.Signal=USART3_TX
PC11.Mode=Asynchronous
PC11.Signal=USART3_RX
PC12.GPIOParameters=GPIO_Label
PC12.GPIO_Label=UART3_GPIO
PC12.Signal=GPIO_Analog
PC13.GPIOParameters=GPIO_Label
PC13.GPIO_Label=I2C1_GPIO8
PC13.Signal=GPIO_Analog
PC2.GPIOParameters=GPIO_Label
PC2.GPIO_Label=I2C2_GPIO8
PC2.Signal=GPIO_Analog
PC6.Signal=S_TIM8_CH1
PC7.Signal=S_TIM8_CH2
PC8.GPIOParameters=GPIO_Label
PC8.GPIO_Label=TIM8_IO
PC8.Signal=GPIO_Analog
PD0.Mode=CAN_Activate
PD0.Signal=CAN1_RX
PD1.Mode=CAN_Activate
PD1.Signal=CAN1_TX
PD10.GPIOParameters=GPIO_Label
PD10.GPIO_Label=TIM2_GPIO
PD10.Signal=GPIO_Analog
PD12.Signal=S_TIM4_CH1
PD13.Signal=S_TIM4_CH2
PD14.GPIOParameters=GPIO_Label
PD14.GPIO_Label=LED1_PWM
PD14.Signal=S_TIM4_CH3
PD15.GPIOParameters=GPIO_Label
PD15.GPIO_Label=LED2_PWM
PD15.Signal=S_TIM4_CH4
PD3.GPIOParameters=GPIO_Label
PD3.GPIO_Label=UART2_GPIO
PD3.Signal=GPXTI3
PD5.Mode=Asynchronous
PD5.Signal=USART2_TX
PD6.Mode=Asynchronous
PD6.Signal=USART2_RX
PE0.GPIOParameters=GPIO_Label
PE0.GPIO_Label=I2C1_GPIO1
PE0.Signal=GPXTI0
PE1.GPIOParameters=GPIO_Label
PE1.GPIO_Label=I2C1_GPIO2
PE1.Signal=GPIO_Analog
PE10.GPIOParameters=GPIO_Label
PE10.GPIO_Label=SPI_IO1
PE10.Signal=GPIO_Output
PE11.GPIOParameters=GPIO_Label
PE11.GPIO_Label=SPI_IO2
PE11.Signal=GPIO_Output
PE12.Mode=Full_Duplex_Master
PE12.Signal=SPI4_SCK
PE13.Mode=Full_Duplex_Master
PE13.Signal=SPI4_MISO
PE14.Mode=Full_Duplex_Master
PE14.Signal=SPI4_MOSI
PE2.GPIOParameters=GPIO_Label
PE2.GPIO_Label=I2C1_GPIO3
PE2.Signal=GPXTI2
PE3.GPIOParameters=GPIO_Label
PE3.GPIO_Label=I2C1_GPIO4
PE3.Signal=GPIO_Analog
PE4.GPIOParameters=GPIO_Label
PE4.GPIO_Label=I2C1_GPIO5
PE4.Signal=GPXTI4
PE5.GPIOParameters=GPIO_Label,GPIO_Mode
PE5.GPIO_Label=I2C1_GPIO6
PE5.GPIO_Mode=GPIO_MODE_ANALOG
PE5.Signal=GPIO_Analog
PE6.GPIOParameters=GPIO_Label
PE6.GPIO_Label=I2C1_GPIO7
PE6.Signal=GPXTI6
PF0.Mode=I2C
PF0.Signal=I2C2_SDA
PF1.Mode=I2C
PF1.Signal=I2C2_SCL
PF11.GPIOParameters=GPIO_Label
PF11.GPIO_Label=PWR_EXT_FAULT
PF11.Signal=GPXTI11
PF12.GPIOParameters=GPIO_Label
PF12.GPIO_Label=PWR_STATUS
PF12.Signal=GPXTI12
PF13.GPIOParameters=GPIO_Label
PF13.GPIO_Label=GPIO1
PF13.Signal=GPXTI13
PF14.GPIOParameters=GPIO_Label
PF14.GPIO_Label=GPIO2
PF14.Signal=GPXTI14
PF15.GPIOParameters=GPIO_Label
PF15.GPIO_Label=GPIO3
PF15.Signal=GPXTI15
PF5.GPIOParameters=GPIO_Label
PF5.GPIO_Label=I2C2_GPIO1
PF5.Signal=GPXTI5
PF6.GPIOParameters=GPIO_Label
PF6.GPIO_Label=I2C2_GPIO2
PF6.Signal=GPIO_Analog
PF7.GPIOParameters=GPIO_Label
PF7.GPIO_Label=I2C2_GPIO3
PF7.Signal=GPXTI7
PF8.GPIOParameters=GPIO_Label
PF8.GPIO_Label=I2C2_GPIO4
PF8.Signal=GPIO_Analog
PF9.GPIOParameters=GPIO_Label
PF9.GPIO_Label=I2C2_GPIO5
PF9.Signal=GPXTI9
PG10.GPIOParameters=GPIO_Label
PG10.GPIO_Label=UART6_GPIO
PG10.Signal=GPXTI10
PG14.Mode=Asynchronous
PG14.Signal=USART6_TX
PG4.GPIOParameters=GPIO_Label
PG4.GPIO_Label=DEBUG_LED_BLUE
PG4.Signal=GPIO_Output
PG5.GPIOParameters=GPIO_Label
PG5.GPIO_Label=DEBUG_LED_GREEN
PG5.Signal=GPIO_Output
PG6.GPIOParameters=GPIO_Label
PG6.GPIO_Label=DEBUG_LED_RED
PG6.Signal=GPIO_Output
PG9.Mode=Asynchronous
PG9.Signal=USART6_RX
PH0/OSC_IN.Mode=HSE-External-Clock-Source
PH0/OSC_IN.Signal=RCC_OSC_IN
PH1/OSC_OUT.Mode=HSE-External-Clock-Source
PH1/OSC_OUT.Signal=RCC_OSC_OUT
RCC.HSE_VALUE=8000000
RCC.SYSCLKFreq_VALUE=168000000
RCC.SYSCLKSource=RCC_SYSCLKSOURCE_PLLCLK
board=custom

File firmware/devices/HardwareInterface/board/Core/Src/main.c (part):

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  HAL_GPIO_WritePin(PWR_EXT_ENABLE_GPIO_Port, PWR_EXT_ENABLE_Pin, GPIO_PIN_RESET);

  /*Configure GPIO pin Output Level */
  HAL_GPIO_WritePin(GPIOG, DEBUG_LED_BLUE_Pin|DEBUG_LED_GREEN_Pin|DEBUG_LED_RED_Pin, GPIO_PIN_RESET);

  /*Configure GPIO pins : I2C1_GPIO3_Pin I2C1_GPIO5_Pin I2C1_GPIO7_Pin I2C1_GPIO1_Pin */
  GPIO_InitStruct.Pin = I2C1_GPIO3_Pin|I2C1_GPIO5_Pin|I2C1_GPIO7_Pin|I2C1_GPIO1_Pin;
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  HAL_GPIO_Init(GPIOE, &GPIO_InitStruct);

  /*Configure GPIO pins : I2C1_GPIO4_Pin I2C1_GPIO6_Pin PE7 PE8
                           PE9 PE15 I2C1_GPIO2_Pin */
  GPIO_InitStruct.Pin = I2C1_GPIO4_Pin|I2C1_GPIO6_Pin|GPIO_PIN_7|GPIO_PIN_8
                          |GPIO_PIN_9|GPIO_PIN_15|I2C1_GPIO2_Pin;
  GPIO_InitStruct.Mode = GPIO_MODE_ANALOG;
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  GPIO_InitStruct.Pull = GPIO_NOPULL;
  HAL_GPIO_Init(GPIOC, &GPIO_InitStruct);

  /*Configure GPIO pins : PF2 PF3 PF4 I2C2_GPIO2_Pin
                           I2C2_GPIO4_Pin PF10 */
  GPIO_InitStruct.Pin = GPIO_PIN_2|GPIO_PIN_3|GPIO_PIN_4|I2C2_GPIO2_Pin
                          |I2C2_GPIO4_Pin|GPIO_PIN_10;
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  GPIO_InitStruct.Pull = GPIO_NOPULL;
  HAL_GPIO_Init(GPIOF, &GPIO_InitStruct);

  /*Configure GPIO pins : I2C2_GPIO1_Pin I2C2_GPIO3_Pin I2C2_GPIO5_Pin PWR_EXT_FAULT_Pin
                           PWR_STATUS_Pin GPIO1_Pin GPIO2_Pin GPIO3_Pin */
  GPIO_InitStruct.Pin = I2C2_GPIO1_Pin|I2C2_GPIO3_Pin|I2C2_GPIO5_Pin|PWR_EXT_FAULT_Pin
                          |PWR_STATUS_Pin|GPIO1_Pin|GPIO2_Pin|GPIO3_Pin;
  GPIO_InitStruct.Mode = GPIO_MODE_IT_RISING;
  GPIO_InitStruct.Pull = GPIO_NOPULL;
  HAL_GPIO_Init(GPIOF, &GPIO_InitStruct);
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  GPIO_InitStruct.Pull = GPIO_NOPULL;
  HAL_GPIO_Init(GPIOB, &GPIO_InitStruct);

  /*Configure GPIO pins : PG0 PG1 PG2 PG3
                           PG7 PG8 PG11 PG12
                           PG13 PG15 */
  GPIO_InitStruct.Pin = GPIO_PIN_0|GPIO_PIN_1|GPIO_PIN_2|GPIO_PIN_3
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  GPIO_InitStruct.Pull = GPIO_NOPULL;
  HAL_GPIO_Init(GPIOD, &GPIO_InitStruct);

  /*Configure GPIO pins : DEBUG_LED_BLUE_Pin DEBUG_LED_GREEN_Pin DEBUG_LED_RED_Pin */
  GPIO_InitStruct.Pin = DEBUG_LED_BLUE_Pin|DEBUG_LED_GREEN_Pin|DEBUG_LED_RED_Pin;
  GPIO_InitStruct.Mode = GPIO_MODE_OUTPUT_PP;
  GPIO_InitStruct.Pull = GPIO_NOPULL;
  GPIO_InitStruct.Speed = GPIO_SPEED_FREQ_LOW;
  HAL_GPIO_Init(GPIOG, &GPIO_InitStruct);

  /*Configure GPIO pin : USER_BUTTON_Pin */
  GPIO_InitStruct.Pin = USER_BUTTON_Pin;
  GPIO_InitStruct.Mode = GPIO_MODE_IT_RISING_FALLING;
  GPIO_InitStruct.Pull = GPIO_NOPULL;
  HAL_GPIO_Init(USER_BUTTON_GPIO_Port, &GPIO_InitStruct);

  /*Configure GPIO pin : UART2_GPIO_Pin */
  GPIO_InitStruct.Pin = UART2_GPIO_Pin;
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
  // CAuDri - If enabled, start recording traces used for debugging with Tracealyzer
  #ifdef DEBUG_USE_TRACE_RECORDER
    HAL_GPIO_WritePin(DEBUG_LED_BLUE_GPIO_Port, DEBUG_LED_BLUE_Pin, GPIO_PIN_SET);
    #ifdef DEBUG_WAIT_FOR_TRACEALYZER
      xTraceEnable(TRC_START_AWAIT_HOST);
    #else
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    // Initialize the logging interface with multiple trace channels
    extern void logger_trace_init();
    logger_trace_init();
    HAL_GPIO_WritePin(DEBUG_LED_BLUE_GPIO_Port, DEBUG_LED_BLUE_Pin, GPIO_PIN_RESET);
  #endif

  osDelay(10);
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
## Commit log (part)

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2025-06-16 add initial README.md
2025-06-16 add initial PCB files
2025-06-16 add .gitignore
2025-06-16 move PCB design files to KiCad folder
2025-06-19 add symbol and footprint libraries
2025-06-19 update library links and add net classes
2025-06-19 add impedance matched net classes
2025-06-20 Initial Repo Setup
2025-06-20 Revert "Merge branch 'main_tmp' into 'main'"
    This reverts merge request !1
2025-06-20 reannotate schematic
2025-06-20 add differential pairs and power traces
2025-06-22 add final traces
2025-06-23 update PCB layout
2025-06-27 finish PCB routing
2025-06-27 change default KiCad schematic font
2025-06-27 add final layout changes before review
2025-06-27 update text layout and fix remaining DRC errors
2025-06-27 add manufacturing files for JLCPCB
2025-06-27 add schematic and rendered board images
2025-08-12 add ESD protection and update footprints
2025-08-12 update JLCPCB manufacturing files
2025-08-13 update impedance matched tracks for default JLCPCB specs (3313)
2025-08-13 update design constraints and via sizes for JLCPCB
2025-08-20 update images and exported files
2025-08-21 add .gitattribute file for correct line endings
2025-08-21 add Dockerfile and devcontainer.json
2025-08-21 add devcontainer setup script for windows
2025-08-21 add udev rules for serial device access
2025-08-21 add shell script for installing and starting the micro-ROS agent
2025-08-21 add VS Code config files
2025-08-21 add clang-format file
2025-08-21 add initial CubeMX .ioc file for the Hardware Interface
2025-08-21 add initial build script
2025-08-21 update .gitignore and move .clang-format
2025-08-23 fix image link in README.md
2025-08-27 add OpenOCD config file
2025-08-27 update udev rules to support generic CMSIS-DAP adaptors
2025-08-27 add CubeMX geneerated code for Hardware Interface
2025-09-01 move CMakeLists.txt to top level device directory and add .hex and .bin conversion
2025-09-01 fix the include path of the linker script in the toolchain file
2025-09-01 add additional tools to the dev container
2025-09-01 add udev rule for the STM32 DFU bootloader
2025-09-01 update OpenOCD config to use a CMSIS-DAP device by default
2025-09-01 update build script for flashing via USB-DFU
2025-09-01 add micro-ROS static library genration
2025-09-01 fix script path in tasks.json
2025-09-06 add trace recorder library and CMakeLists.txt
2025-09-06 add custom CMakeLists.txt and common CMake include file
2025-09-06 add build script to Dockerfile and update path to the toolchain file
2025-09-06 add trace recorder init and jump to main application entry
2025-09-06 add config files for Hardware Interface
2025-09-06 add thread-safe logging interface
2025-09-07 update dependencies in the Dockerfile
2025-09-07 enable EXTI interrupts in CubeMX and change USB device descriptor
2025-09-09 enable UART callback registering
2025-09-10 enable global UART interrupts
2025-09-10 add USB CDC output to logging interface and remove config struct
2025-09-10 fully integrate Tracelyzer trace recorder library
2025-09-10 enable printf float formatting and set C99 standard
2025-09-30 increase log queue size
2025-09-30 add callback wrapper for different callback types
2025-09-30 add common driver interface
2025-09-30 add initial CRSF/Remote Control driver
2025-09-30 add simple RC Receiver test in main.cpp
2025-10-11 update README with hardware information
2025-10-11 add CERN OHL license copy
2025-10-28 update udev rules to only match STM in bootloader mode
2025-10-28 rename default debug launch config
2025-10-28 add manual forward declaration of the HAL peripheral handles
2025-10-28 add thread-safe I2C wrapper
2025-10-28 add thread-safe CAN bus wrapper and RX dispatcher
2025-10-29 enable CAN interrupts in CubeMX
2025-10-29 update can config
2025-10-30 add init for thread safe HAL extensions
2025-10-30 add callback registry for can wrapper
2025-10-30 add hard coded MCU definition for CMSIS
2025-10-30 fix const member naming for RC receiver
2025-10-30 add common compiler and linker flags
2025-10-30 add initial servo driver implementation
2025-10-30 add initial VESC driver implementation
2025-10-30 update main.cpp with exmaple driver test
2025-11-15 increase clang-format column limit
2025-11-15 add more robust USB handling for the logger
2025-11-15 lower log verbosity for the thread-safe CAN interface
2025-11-15 enable flashing via ST-Link
2025-11-15 update RC receiver with proper state and error handling
2025-11-15 add connection state handling to driver interface
2025-11-27 PCB: update resistor values and embed font
2025-11-27 PCB: fix silkscreen pinout for servo and CAN connectors
2025-11-29 PCB: change revision and dates
2025-11-30 PCB: update drawing sheet
2025-11-30 PCB: add manufacturing files for v1.1
2025-11-30 PCB: update exported files
2025-11-30 PCB: fix manufacturing files for v1.1
2025-11-30 fix trace recorder init for globally declared driver instances
2025-11-30 add simple state handling and safety to VESC driver
2025-12-04 update CubeMX and HAL version and link DMA stream for WS2812
2025-12-05 add channel definitions to CRSF protocol
2025-12-05 add RC receiver callback for all channels
2025-12-06 add SystemCheck class
2025-12-06 add DriveController for mode switch and motor control
2025-12-06 add driver for WS2812
2025-12-06 add Color class for RGB and HSV color representations
2025-12-06 add Light interface
2025-12-06 add WS2812 Light implementation for subsets of a LED string
2025-12-06 add Animation interface and blink and pulse animations
2025-12-06 move RC receiver definitions to .cpp file
2025-12-06 add debug message to hard fault handler
2025-12-06 add global symbols for linking/debugging
2025-12-06 fix CubeMX generated USB serial descriptor
2025-12-07 fix VESC callback registering and add remaining status handlers
2025-12-07 add proper connection state handling to VESC driver
2025-12-07 refactor Color class
2025-12-08 add Light interface implementation for single GPIO controlled LEDs
2025-12-08 fix validation for system check warnings
2025-12-08 change log level for DriveController init
2025-12-08 add SystemMonitor for background system checks
2025-12-08 magically fix log output on stack overflow by simply changing the message
2025-12-08 add missing state change publishing to RC receiver
2025-12-08 add verbose log to servo driver
2025-12-08 update WS2812 connection state after init
2025-12-08 add missing include for hardfault handler
2025-12-08 add stack overflow and malloc failure hooks for the Hardware Interface
2025-12-08 add missing DMA stream declaration to main.h
2025-12-08 update FreeRTOS CubeMX config
2025-12-08 Dev Container: fix paths in windows install script
2025-12-11 fix missing declaration in system monitor
2025-12-12 enable TIM5 for ADC sampling
2025-12-13 enable DMA streams for ADC peripherals
2026-02-03 PCB: move LED2 to timer peripheral 1 and update pinout
2026-02-27 PCB: add XOR gate for RC Receiver
2026-02-27 update .ioc with new pin layout
2026-03-08 PCB: update manufacturing files

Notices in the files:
firmware/devices/HardwareInterface/board/Core/Src/main.c:
Copyright (c) 2025 STMicroelectronics.
All rights reserved.
This software is licensed under terms that can be found in the LICENSE file
PCB/KiCad/hardware_interface.kicad_pcb:
Redistribution and modifications must comply with CERN-OHL-W v2.
This design is licensed under CERN Open Hardware Licence Version 2.
Licensed under CERN OHL-W v2
